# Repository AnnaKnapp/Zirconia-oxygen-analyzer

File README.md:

This repository contains the hardware design files and software for a high precision oxygen analyzer.

Analyzer hardware description:
The analyzer uses a fast-response dual-cell zirconia oxygen sensor manufactured by Process Sensing Technologies. A thermocouple probe is fitted into the sensor to enable a PID controller to hold the sensing element at a constant temperature. An analog feedback loop based on the one described by Benammar and Maskell (Benamar, 1993) holds the average O2 partial pressure inside the sealed central chamber of the sensor at a fixed ratio with that of the external sample gas. A 16-bit digital-to-analog-converter (DAC) is used to generate a 1 Hz sinusoidal waveform to pump oxygen into and out of the central chamber using the pumping cell. The digital pumping signal is controlled by a custom-built digital lock-in amplifier. The Nernst potential generated across the sensing cell is digitized with a 32-bit analog-to-digital converter. The amplitude and phase of the sense signal is calculated by the lock-in amplifier and a 10-second moving average filter is applied.

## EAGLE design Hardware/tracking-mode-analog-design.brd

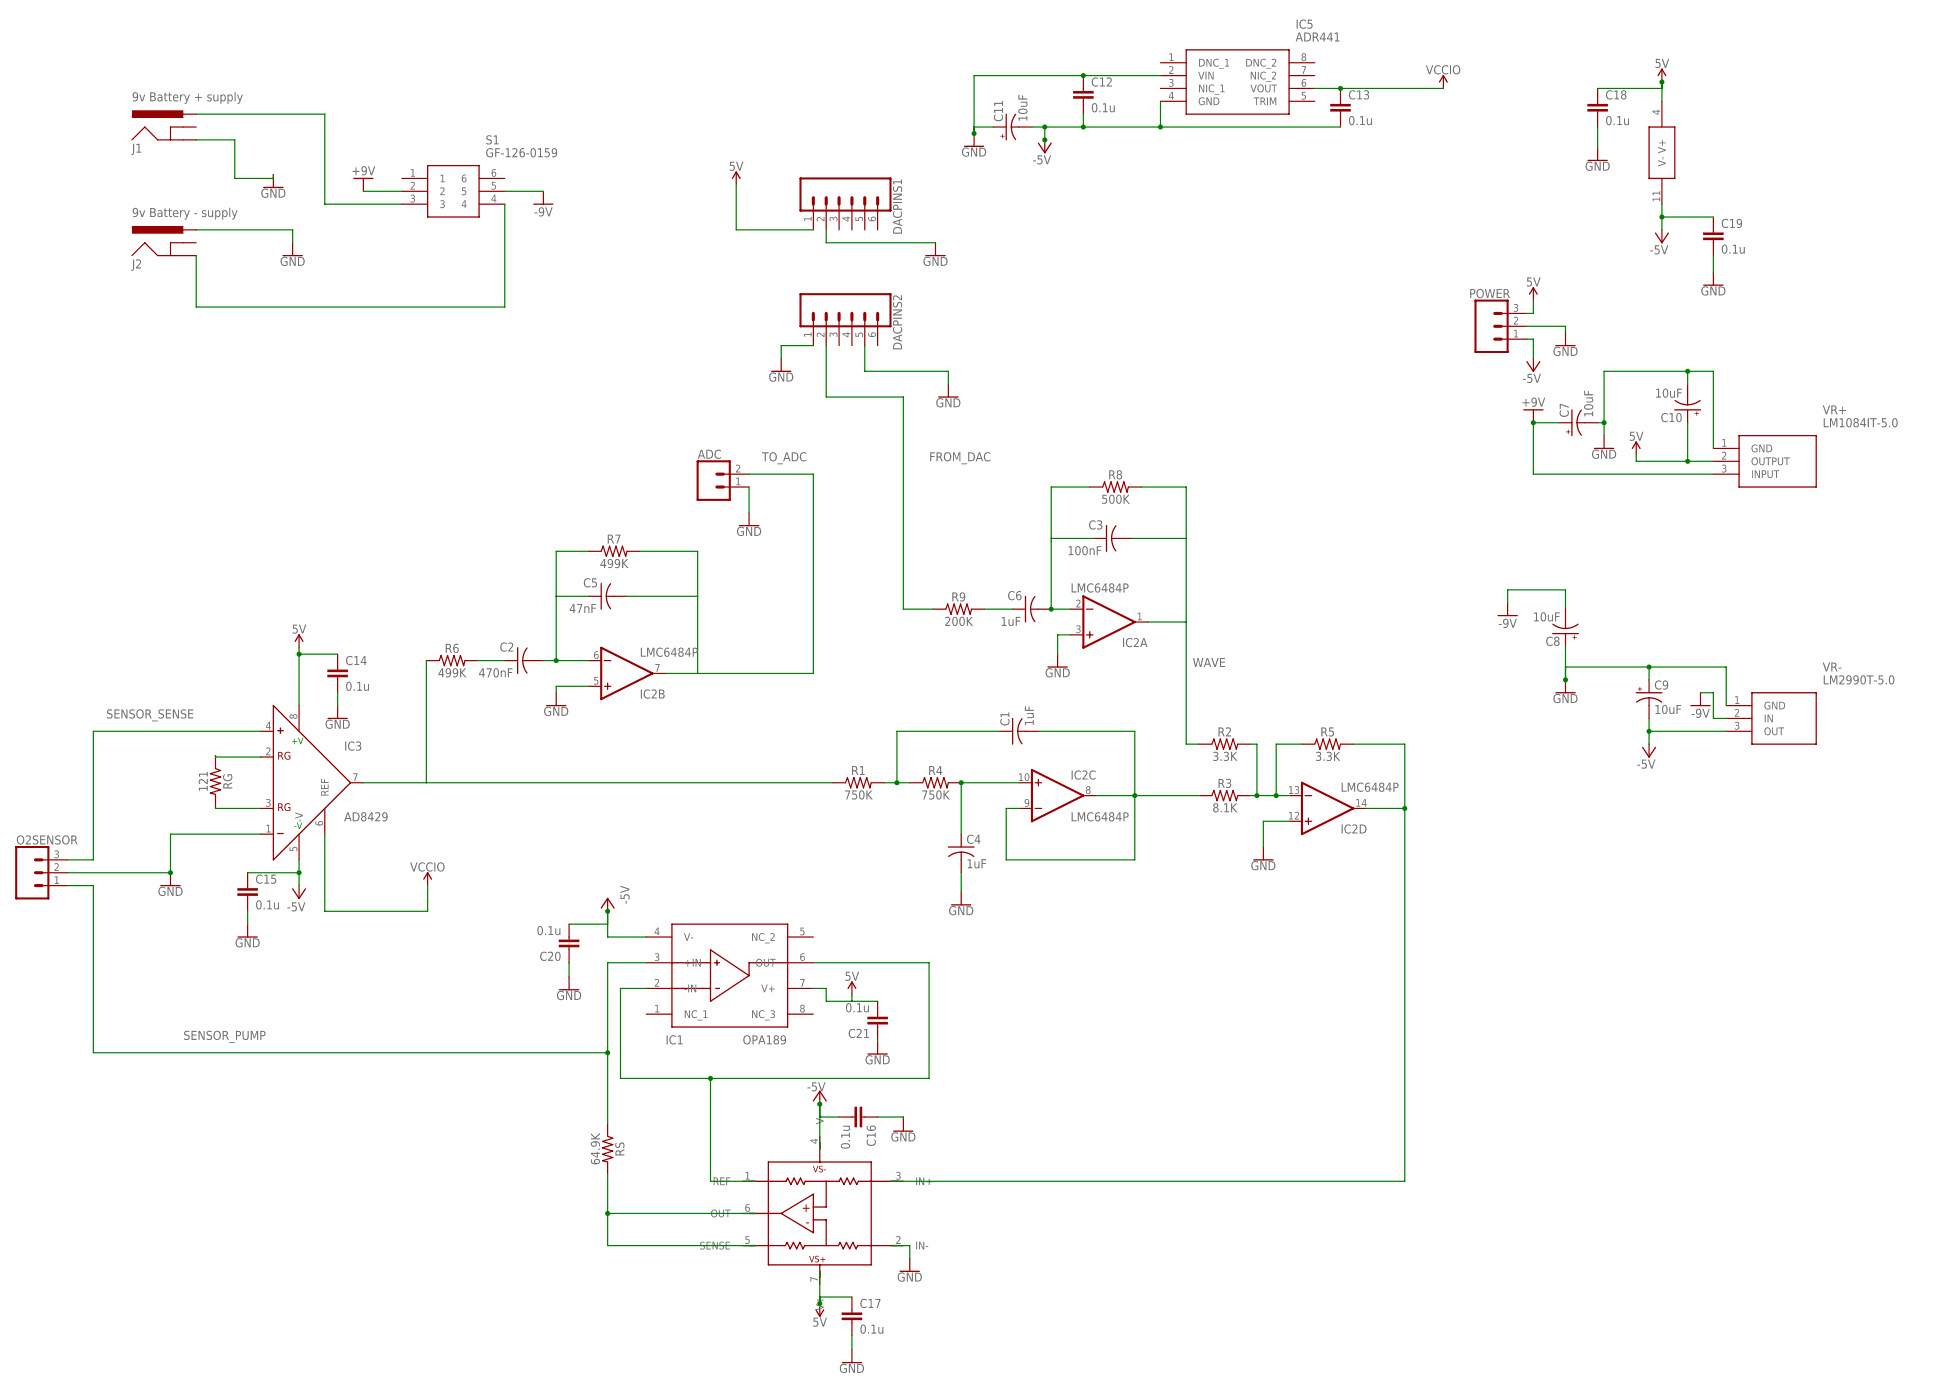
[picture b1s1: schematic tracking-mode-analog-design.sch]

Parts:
ADC: CONN_02; 1X02
C1, C4, C6: 1uF; C025-030X050
C2: 470nF; C025-030X050
C3: 100nF; C025-030X050
C5: 47nF; C025-030X050
C7, C8, C9, C10, C11: 10uF; CPOL-RADIAL-2.5MM-5MM-KIT
C12, C13, C14, C15, C16, C17, C18, C19, C20, C21: 0.1u; C025-040X050
DACPINS1, DACPINS2: CONN_06SILK_FEMALE_PTH; 1X06
IC1: OPA189; SOIC127P600X175-8N
IC2: LMC6484P; DIL14
IC3: AD8429; SO8
IC5: ADR441; SOIC127P600X175-8N
INA592: INA592; SO08
J1: 9v Battery + supply; POWER_JACK_PTH_BREAD
J2: 9v Battery - supply; POWER_JACK_PTH_BREAD
O2SENSOR: CONN_03; 1X03
POWER: CONN_03; 1X03
R1, R4: 750K; AXIAL-0.3
R2, R5: 3.3K; AXIAL-0.3
R3: 8.1K; AXIAL-0.3
R6, R7: 499K; AXIAL-0.3
R8: 500K; AXIAL-0.3
R9: 200K; AXIAL-0.3
RG: 121; AXIAL-0.3
RS: 64.9K; AXIAL-0.3
S1: GF-126-0159; GF1260159
VR+: LM1084IT-5.0; TO254P470X1028X1955-3P
VR-: LM2990T-5.0; TO254P470X1028X1955-3P

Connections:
5V: C10.1 (+), C14.1, C17.1, C18.1, C21.2, DACPINS1.1, IC1.7 (V+), IC2.4 (V+), IC3.8 (+V), INA592.7 (V+), POWER.3, VR+.2 (OUTPUT)
+V: C7.1 (+), S1.2, VR+.3 (INPUT)
-5V: C9.2 (-), C11.2 (-), C12.2, C13.2, C15.1, C16.2, C19.1, C20.2, IC1.4 (V-), IC2.11 (V-), IC3.5 (-V), IC5.4 (GND), INA592.4 (V-), POWER.1, VR-.3 (OUT)
-V: C8.2 (-), S1.5, VR-.2 (IN)
FROM_DAC: DACPINS2.2, R9.P$1 (1)
GND: ADC.1, C4.2, C7.2 (-), C8.1 (+), C9.1 (+), C10.2 (-), C11.1 (+), C12.1, C14.2, C15.2, C16.1, C17.2, C18.2, C19.2, C20.1, C21.1, DACPINS1.2, DACPINS2.1, DACPINS2.5, IC2.3 (+IN), IC2.5 (+IN), IC2.12 (+IN), IC3.1 (-), IC5.2 (VIN), INA592.2 (IN-), J1.GND, J2.PWR, O2SENSOR.2, POWER.2, VR+.1 (GND), VR-.1 (GND)
unnamed: C2.2, C5.1, IC2.6 (-IN), R7.P$1 (1)
unnamed: INA592.5 (SENSE), INA592.6 (OUT), RS.P$2 (2)
unnamed: C2.1, R6.P$2 (2)
unnamed: IC3.7 (OUT), R1.P$1 (1), R6.P$1 (1)
unnamed: C1.1, R1.P$2 (2), R4.P$1 (1)
unnamed: C4.1, IC2.10 (+IN), R4.P$2 (2)
unnamed: C1.2, IC2.8 (OUT), IC2.9 (-IN), R3.P$1 (1)
unnamed: IC2.13 (-IN), R2.P$2 (2), R3.P$2 (2), R5.P$1 (1)
unnamed: IC1.2 (-IN), IC1.6 (OUT), INA592.1 (REF)
unnamed: IC2.14 (OUT), INA592.3 (IN+), R5.P$2 (2)
unnamed: C6.1, R9.P$2 (2)
unnamed: IC3.2 (RG), RG.P$1 (1)
unnamed: C3.1, C6.2, IC2.2 (-IN), R8.P$1 (1)
unnamed: J2.GND, S1.4
unnamed: J1.PWR, S1.3
unnamed: IC3.3 (RG), RG.P$2 (2)
SENSOR_PUMP: IC1.3 (+IN), O2SENSOR.1, RS.P$1 (1)
SENSOR_SENSE: IC3.4 (+), O2SENSOR.3
TO_ADC: ADC.2, C5.2, IC2.7 (OUT), R7.P$2 (2)
VCCIO: C13.1, IC3.6 (REF), IC5.6 (VOUT)
WAVE: C3.2, IC2.1 (OUT), R2.P$1 (1), R8.P$2 (2)

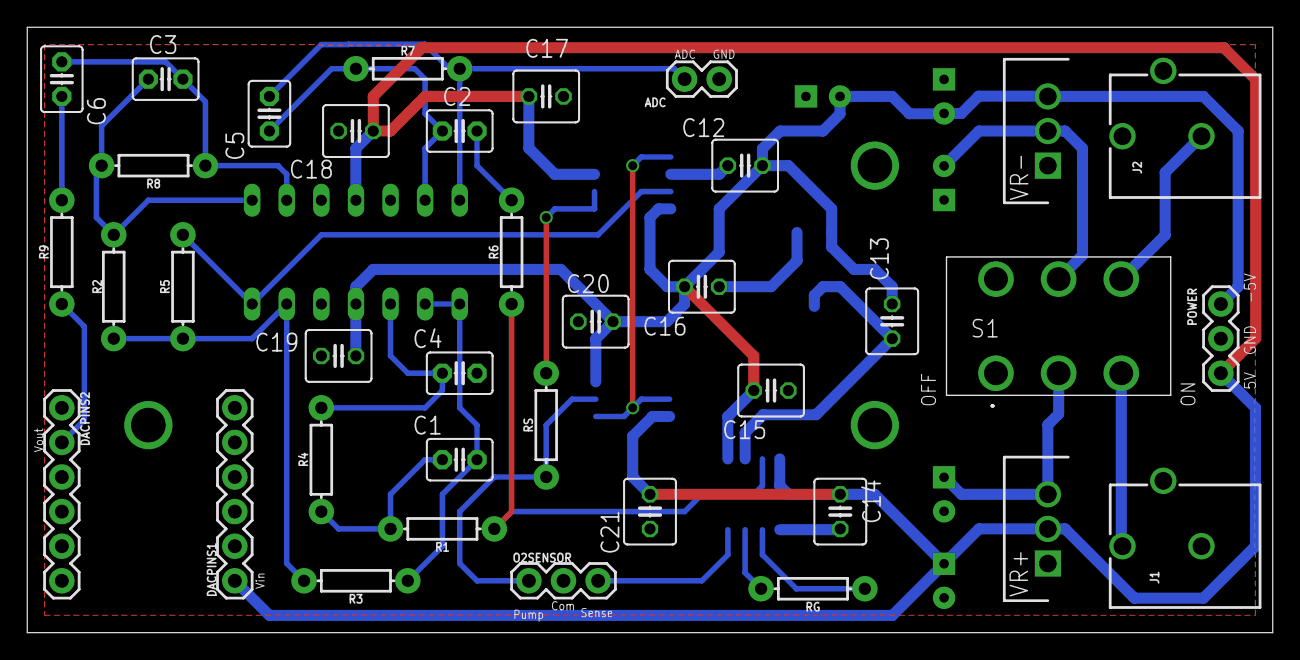
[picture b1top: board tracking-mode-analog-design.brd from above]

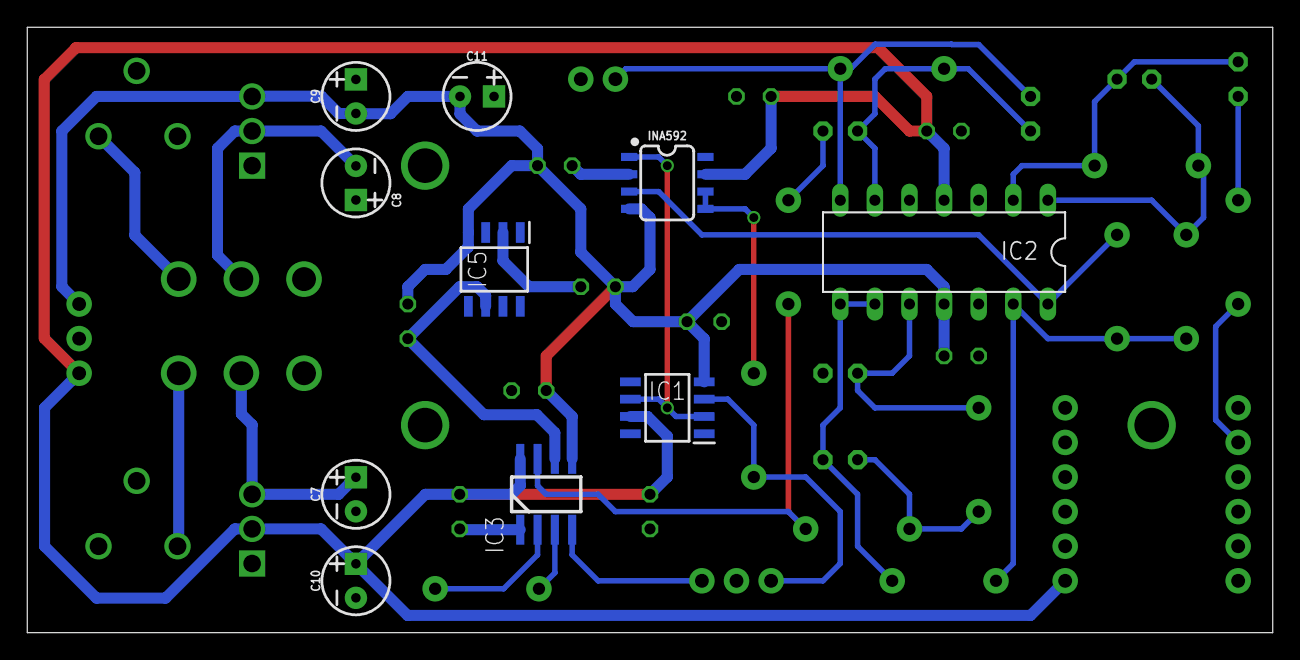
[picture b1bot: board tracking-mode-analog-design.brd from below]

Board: 2 copper layers, 91.4 x 44.5 mm, 47 parts (10 on the bottom side), 27 nets.

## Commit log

2024-07-02 Update LICENSE to CERN-OHL-W
2024-07-02 Added arduino code for MCU
2024-07-02 Added python script for lock-in-amplifier
2024-07-05 added eagle files for schematic and board

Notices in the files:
parts and their libraries:
SparkFun-Connectors: Licensing: Creative Commons ShareAlike 4.0 International - https://creativecommons.org/licenses/by-sa/4.0
